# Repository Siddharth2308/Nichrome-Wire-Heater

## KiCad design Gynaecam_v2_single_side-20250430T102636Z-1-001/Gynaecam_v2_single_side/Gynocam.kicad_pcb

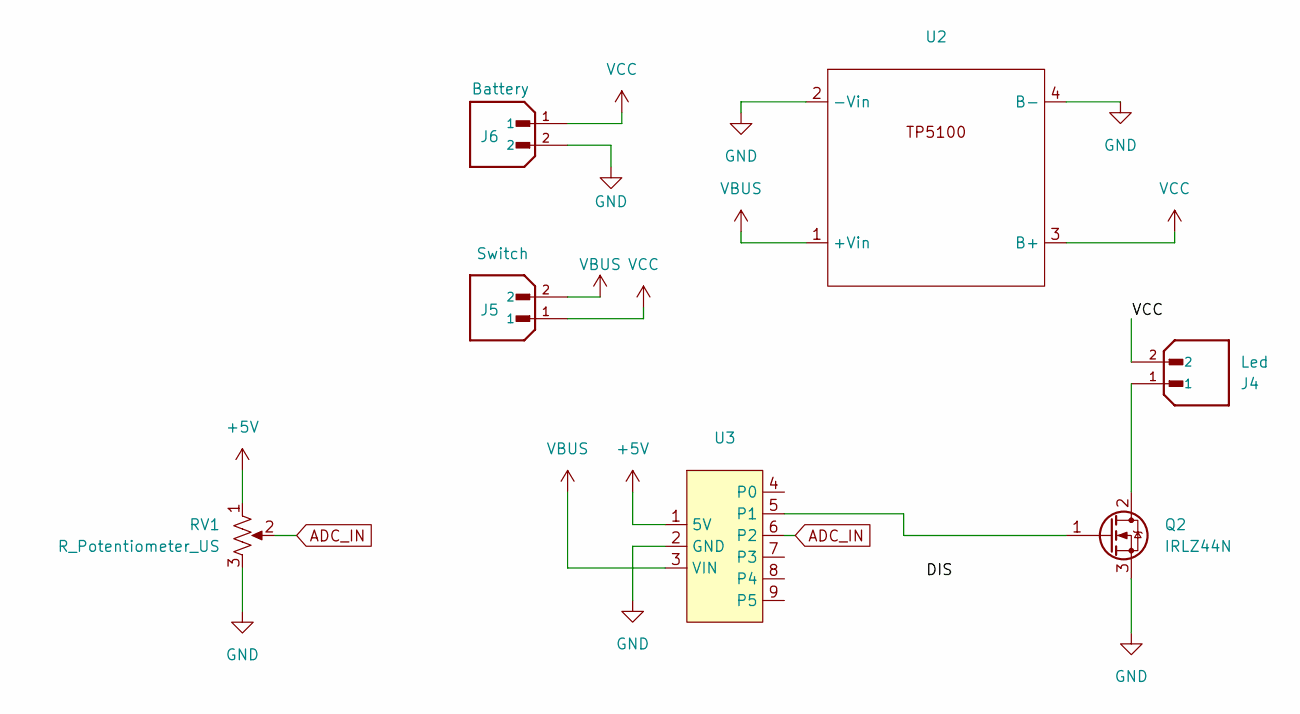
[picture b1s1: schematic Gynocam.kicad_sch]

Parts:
J4: Led; Molex_KK-254_AE-6410-02A_1x02_P2.54mm_Vertical; PARTREV N/A
J5: Switch; Molex_KK-254_AE-6410-02A_1x02_P2.54mm_Vertical; PARTREV N/A
J6: Battery; Molex_KK-254_AE-6410-02A_1x02_P2.54mm_Vertical; PARTREV N/A
Q2: IRLZ44N; TO-220-3_Vertical
RV1: R_Potentiometer_US; Molex_KK-254_AE-6410-03A_1x03_P2.54mm_Vertical
U2: TP5100
U3: attiny85-digispark

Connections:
+5V: RV1.1, U3.1 (5V)
ADC_IN: RV1.2, U3.6 (P2)
GND: J6.2, Q2.3 (S), RV1.3, U2.2 (-Vin), U2.4 (B-), U3.2 (GND)
unnamed: J4.1, Q2.2 (D)
unnamed: Q2.1 (G), U3.5 (P1)
VBUS: J5.2, U2.1 (+Vin), U3.3 (VIN)
VCC: J4.2, J5.1, J6.1, U2.3 (B+)

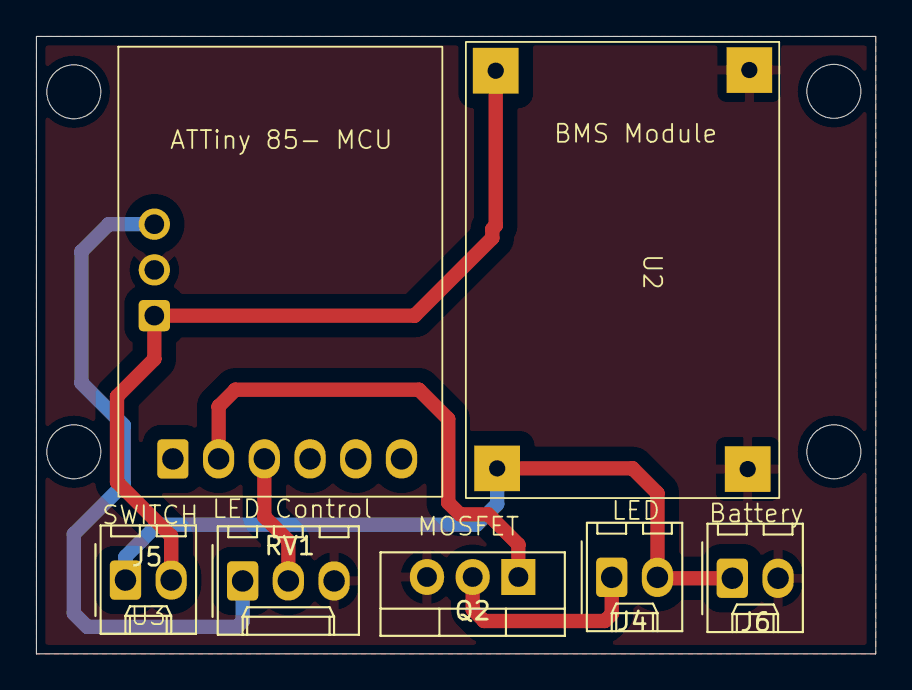
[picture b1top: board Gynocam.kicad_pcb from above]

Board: 2 copper layers, 46.6 x 34.3 mm, 7 parts (0 on the bottom side), 7 nets.

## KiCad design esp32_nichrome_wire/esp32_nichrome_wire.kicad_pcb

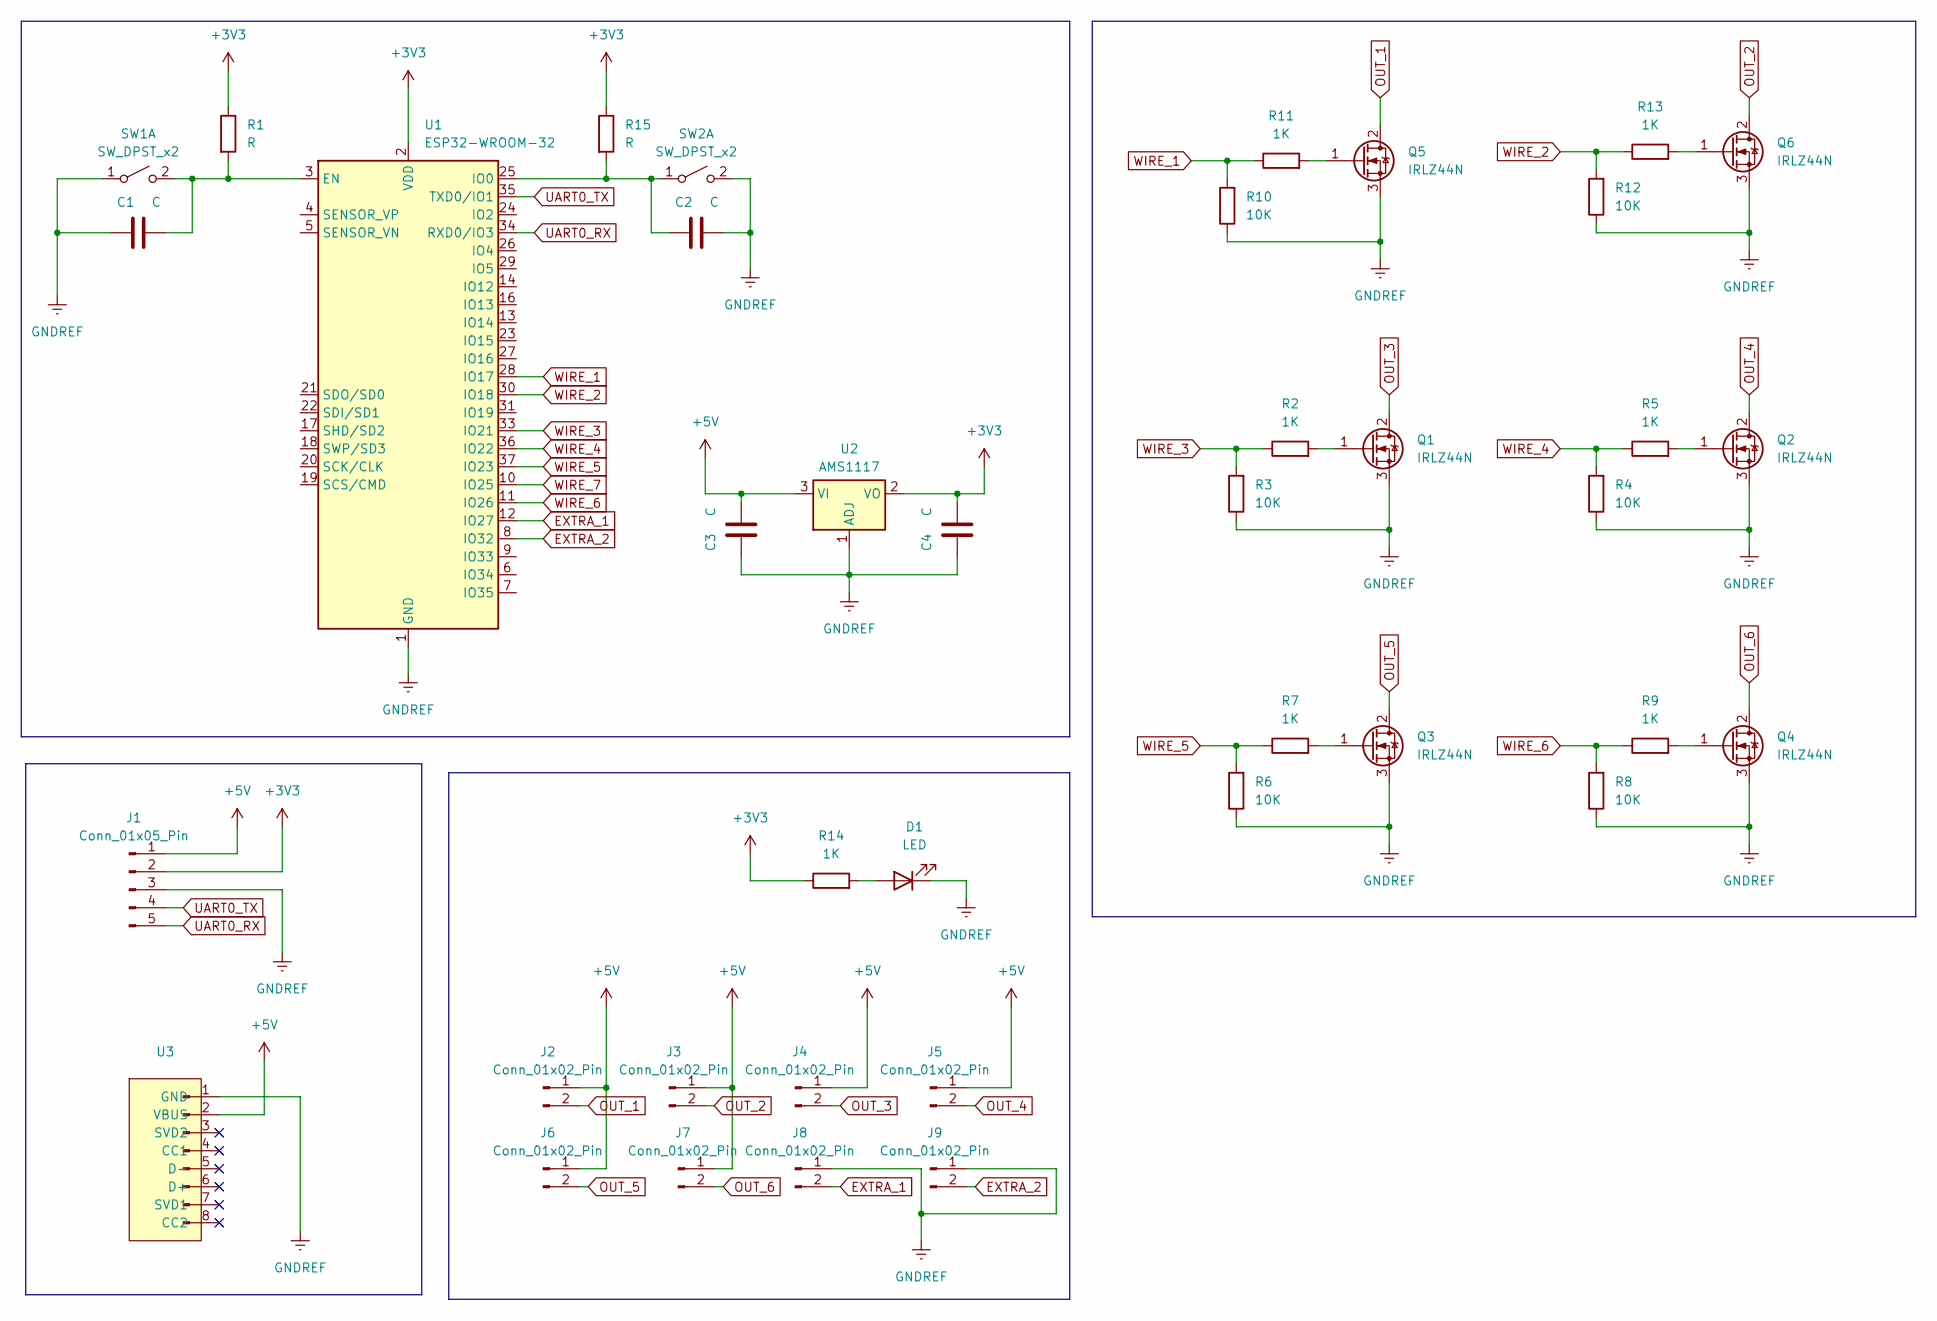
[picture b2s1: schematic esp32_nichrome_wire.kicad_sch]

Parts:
C1, C2, C3, C4: C; C_1206_3216Metric_Pad1.33x1.80mm_HandSolder
D1: LED; LED_1206_3216Metric
J1: Conn_01x05_Pin; PinSocket_1x05_P2.54mm_Vertical
J2, J3, J4, J5, J6, J7, J8, J9: Conn_01x02_Pin; Molex_KK-254_AE-6410-02A_1x02_P2.54mm_Vertical
Q1, Q2, Q3, Q4, Q5, Q6: IRLZ44N; TO-220-3_Vertical
R1, R15: R; R_1206_3216Metric
R2, R5, R7, R9, R11, R13, R14: 1K; R_1206_3216Metric
R3, R4, R6, R8, R10, R12: 10K; R_1206_3216Metric
SW1, SW2: SW_DPST_x2; SW_SPST_B3U-1000P
U1: ESP32-WROOM-32
U2: AMS1117; SOT-223-3_TabPin2
U3: usb-c-breakout

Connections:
+3V3: C4.2, J1.2, R1.1, R14.1, R15.1, U1.2 (VDD), U2.2 (VO)
+5V: C3.2, J1.1, J2.1, J3.1, J4.1, J5.1, J6.1, J7.1, U2.3 (VI), U3.2 (VBUS)
EXTRA_1: J8.2, U1.12 (IO27)
EXTRA_2: J9.2, U1.8 (IO32)
GNDREF: C1.1, C2.2, C3.1, C4.1, D1.1 (K), J1.3, J8.1, J9.1, Q1.3 (S), Q2.3 (S), Q3.3 (S), Q4.3 (S), Q5.3 (S), Q6.3 (S), R3.1, R4.1, R6.1, R8.1, R10.1, R12.1, SW1.1 (A), SW2.2 (B), U1.1 (GND), U1.15 (GND), U1.38 (GND), U1.39 (GND), U2.1 (ADJ), U3.1 (GND)
unnamed: D1.2 (A), R14.2
unnamed: Q1.1 (G), R2.2
unnamed: Q2.1 (G), R5.2
unnamed: Q3.1 (G), R7.2
unnamed: Q4.1 (G), R9.2
unnamed: Q5.1 (G), R11.2
unnamed: Q6.1 (G), R13.2
unnamed: C1.2, R1.2, SW1.2 (B), U1.3 (EN)
unnamed: C2.1, R15.2, SW2.1 (A), U1.25 (IO0)
OUT_1: J2.2, Q5.2 (D)
OUT_2: J3.2, Q6.2 (D)
OUT_3: J4.2, Q1.2 (D)
OUT_4: J5.2, Q2.2 (D)
OUT_5: J6.2, Q3.2 (D)
OUT_6: J7.2, Q4.2 (D)
UART0_RX: J1.5, U1.34 (RXD0/IO3)
UART0_TX: J1.4, U1.35 (TXD0/IO1)
WIRE_1: R10.2, R11.1, U1.28 (IO17)
WIRE_2: R12.2, R13.1, U1.30 (IO18)
WIRE_3: R2.1, R3.2, U1.33 (IO21)
WIRE_4: R4.2, R5.1, U1.36 (IO22)
WIRE_5: R6.2, R7.1, U1.37 (IO23)
WIRE_6: R8.2, R9.1, U1.11 (IO26)
WIRE_7: U1.10 (IO25)

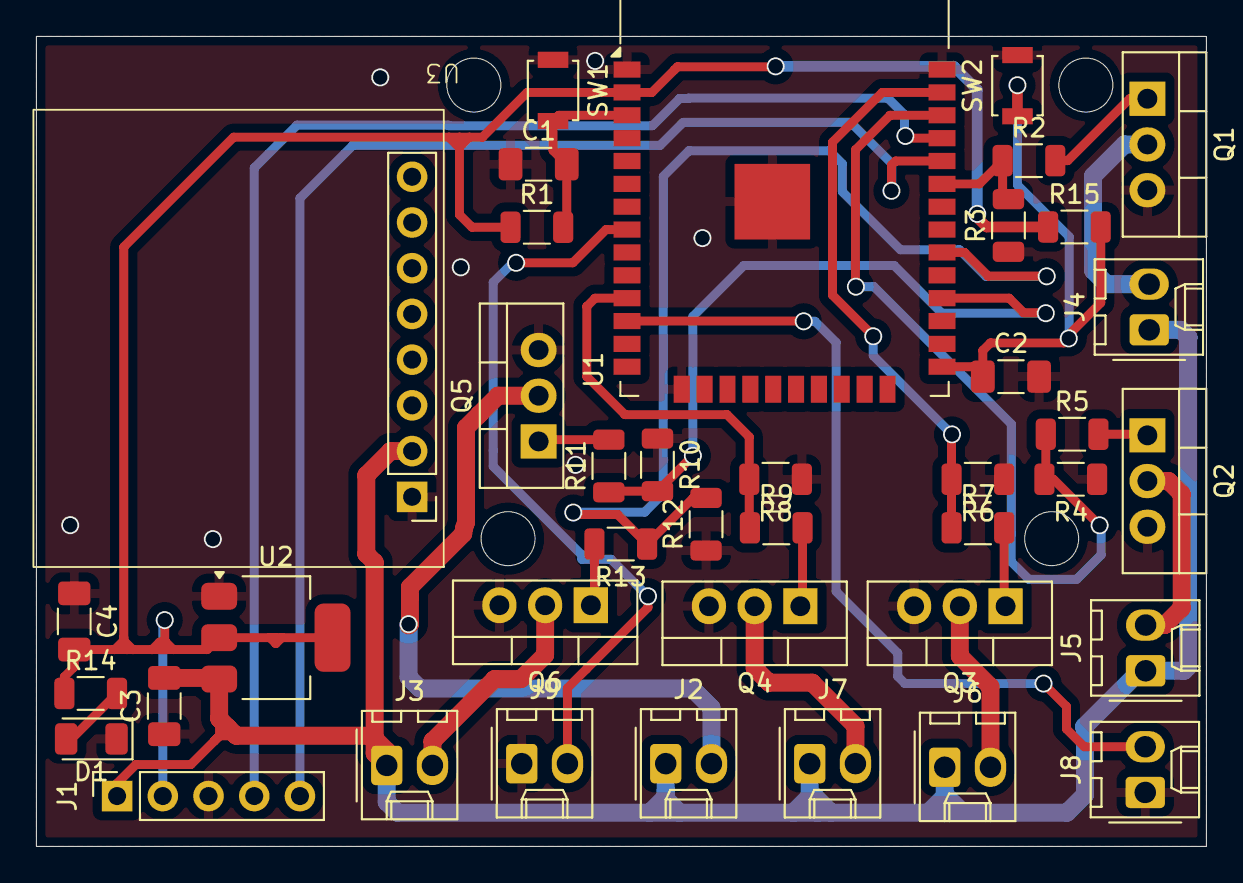
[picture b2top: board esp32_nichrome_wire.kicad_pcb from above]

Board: 2 copper layers, 65.0 x 45.0 mm, 40 parts (0 on the bottom side), 28 nets.

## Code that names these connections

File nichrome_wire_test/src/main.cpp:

#include <Arduino.h>
#include <WiFi.h>
#include <ESPAsyncWebServer.h>
#include "SPIFFS.h"

const char* ssid = "Heat Control";
const char* password = ""; // No password for open network

#define WIRE_1 21
#define WIRE_2 22
#define WIRE_3 23
#define WIRE_4 25
#define WIRE_5 26
#define WIRE_6 17
#define WIRE_7 18

#define WIRE_1_CHANNEL 1
#define WIRE_2_CHANNEL 2
#define WIRE_3_CHANNEL 3
#define WIRE_4_CHANNEL 4
#define WIRE_5_CHANNEL 5
#define WIRE_6_CHANNEL 6
#define WIRE_7_CHANNEL 7


#define PWM_RES 8
#define PWM_FREQ 1000
#define PWM_SETUP ledcSetup
#define PWM_ATTACH ledcAttachPin
#define SET_PWM ledcWrite

int data;
int pin_array[] = {0, WIRE_1, WIRE_2, WIRE_3, WIRE_4, WIRE_5, WIRE_6, WIRE_7};

AsyncWebServer server(80);
void initSoftAP();
void updatePWM(String userId, int pwmValue);

void setup() {
  // put your setup code here, to run once:
  Serial.begin(115200);
  initSoftAP();


  pinMode(WIRE_1, OUTPUT);
  pinMode(WIRE_2, OUTPUT);
  pinMode(WIRE_3, OUTPUT);
  pinMode(WIRE_4, OUTPUT);
  pinMode(WIRE_5, OUTPUT);
  pinMode(WIRE_6, OUTPUT);
  pinMode(WIRE_7, OUTPUT);

  PWM_SETUP(0, PWM_FREQ, PWM_RES);
  PWM_ATTACH(WIRE_1, WIRE_1_CHANNEL);
  PWM_ATTACH(WIRE_2, WIRE_2_CHANNEL);
  PWM_ATTACH(WIRE_3, WIRE_3_CHANNEL);
  PWM_ATTACH(WIRE_4, WIRE_4_CHANNEL);
  PWM_ATTACH(WIRE_5, WIRE_5_CHANNEL);
  PWM_ATTACH(WIRE_6, WIRE_6_CHANNEL);
  PWM_ATTACH(WIRE_7, WIRE_7_CHANNEL);

  for (int i = 0; i < sizeof(pin_array) / sizeof(pin_array[0]); i++) {
    PWM_SETUP(i, PWM_FREQ, PWM_RES);
    PWM_ATTACH(pin_array[i], i);
    SET_PWM(i, 0); // Initialize all channels to 0
  }


  if (!SPIFFS.begin(true)) {
    Serial.println("SPIFFS mount failed");
    return;
  }

  server.on("/", HTTP_GET, [](AsyncWebServerRequest * request) {
    request->send(SPIFFS, "/index.html", "text/html");
  });

  server.on("/temperature", HTTP_GET, [](AsyncWebServerRequest *request) {
    if (request->hasParam("value") && request->hasParam("wire")) {
      String pwmValueStr = request->getParam("value")->value();
      String userId = request->getParam("wire")->value();
      int pwmValue = pwmValueStr.toInt();
      updatePWM(userId, pwmValue);
      request->send(200, "text/plain", "PWM updated");
    } else {
      request->send(400, "text/plain", "Invalid parameters");
    }
  });

  server.begin();
}

void loop() {
  // put your main code here, to run repeatedly:
  if(Serial.available() > 2){
    data = Serial.parseInt();
    SET_PWM(WIRE_1_CHANNEL, data);
    SET_PWM(WIRE_2_CHANNEL, data);
    SET_PWM(WIRE_3_CHANNEL, data);
    SET_PWM(WIRE_4_CHANNEL, data);
    SET_PWM(WIRE_5_CHANNEL, data);
    SET_PWM(WIRE_6_CHANNEL, data);
    SET_PWM(WIRE_7_CHANNEL, data);

    Serial.print("PWM set to: ");Serial.println(data);
  }
}

void initSoftAP() {
  // Start the SoftAP
  if (WiFi.softAP(ssid, password)) {
    Serial.println("SoftAP initialized successfully.");
    Serial.print("SSID: ");
    Serial.println(ssid);
    Serial.print("IP Address: ");
    Serial.println(WiFi.softAPIP());
  } else {
    Serial.println("Failed to initialize SoftAP.");
  }
}

void updatePWM(String userId, int pwmValue) {
  // Convert userId to integer
  int wireIndex = userId.toInt();

  // Validate wireIndex to ensure it corresponds to a valid channel
  if (wireIndex >= 0 && wireIndex <= 7) {
    int channel = wireIndex; // Map wireIndex to channel (WIRE_3_CHANNEL to WIRE_7_CHANNEL)
    SET_PWM(channel, pwmValue); // Update PWM for the respective channel
    Serial.print("PWM updated for wire ");
    Serial.print(wireIndex);
    Serial.print(" (channel ");
    Serial.print(channel);
    Serial.print("): ");
    Serial.println(pwmValue);
  } else {
    Serial.print("Wire:");Serial.print(wireIndex);
    Serial.print(" PWM:");Serial.print(pwmValue);
    Serial.println("Invalid wire index received.");

  }
}

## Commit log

2025-05-30 Init
2025-05-30 temp project added
2025-06-27 suii
